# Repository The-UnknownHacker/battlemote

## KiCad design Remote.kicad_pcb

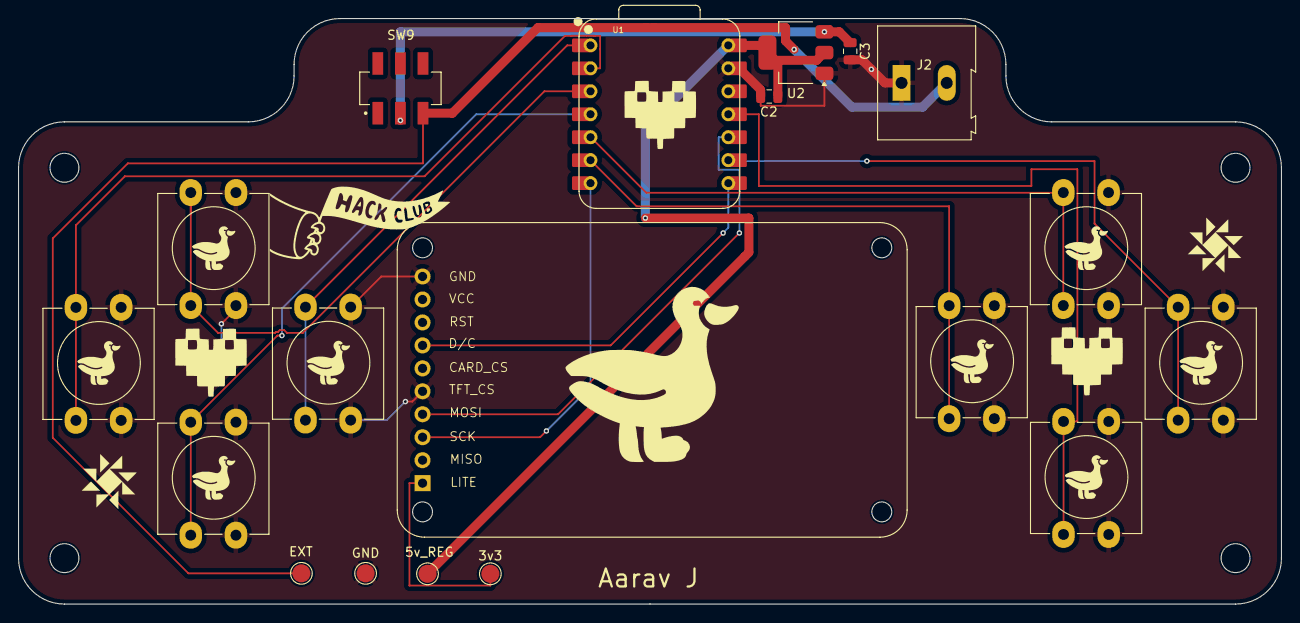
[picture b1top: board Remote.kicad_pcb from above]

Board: 2 copper layers, 139.7 x 64.8 mm, 23 parts (1 on the bottom side), 16 nets.

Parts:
3v3, 5v_REG: TestPoint; TestPoint_Pad_D2.0mm
C2, C3: 22uf; C_0805_2012Metric
EXT: TestPoint; TestPoint_Pad_D2.0mm
GND: TestPoint; TestPoint_Pad_D2.0mm
H1, H2, H3, H4: MountingHole; MountingHole_3.2mm_M3
J2: Extra Battery; TerminalBlock_Altech_AK300-2_P5.00mm
SW1: Right; SW_PUSH-12mm_Wuerth-430476085716
SW2: Left; SW_PUSH-12mm_Wuerth-430476085716
SW3: Top; SW_PUSH-12mm_Wuerth-430476085716
SW4: Bottom; SW_PUSH-12mm_Wuerth-430476085716
SW5: CONFIG1; SW_PUSH-12mm_Wuerth-430476085716
SW6: CONFIG2; SW_PUSH-12mm_Wuerth-430476085716
SW7: CONFIG3; SW_PUSH-12mm_Wuerth-430476085716
SW8: CONFIG4; SW_PUSH-12mm_Wuerth-430476085716
SW9: Slideswitch; SW_JS202011SCQN
U1: XIAO-ESP32-C3-DIP; XIAO-ESP32C3-DIP
U2: AMS1117-5.0; SOT-223-3_TabPin2
U3: 358; MODULE_358

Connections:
+3V3: 3v3.1, U1.12 (VCC_3V3), U3.1 (LITE), U3.8 (RESET), U3.9 (VCC)
+5v_REG: 5v_REG.1, C2.2, U1.14 (VBUS), U2.2 (VO)
EXTERNAL_BAT: EXT.1, J2.2, SW9.3 (C)
GND: C2.1, C3.1, GND.1, J2.1, SW1.2, SW2.2, SW3.2, SW4.2, SW5.2, SW6.2, SW7.2, SW8.2, U1.13 (GND), U2.1 (GND), U3.5 (TFT_CS), U3.10 (GND)
GPIO2: SW1.1, U1.1 (GPIO2/A0/D0)
GPIO3: SW2.1, U1.2 (GPIO3/A1/D1)
GPIO4: SW3.1, U1.3 (GPIO4/A2/D2)
GPIO5: SW4.1, U1.4 (GPIO5/A3/D3)
GPIO6: SW5.1, U1.5 (GPIO6/D4/SDA)
GPIO7: SW6.1, U1.6 (GPIO7/D5/SCL)
GPIO8: SW7.1, U1.9 (GPIO8/D8/SCK)
GPIO9: U1.10 (GPIO9/D9/MISO), U3.4 (MOSI)
GPIO10: SW8.1, U1.11 (GPIO10/D10/MOSI)
GPIO20: U1.8 (GPIO20/D7/RX), U3.7 (D/C)
GPIO21: U1.7 (GPIO21/D6/TX), U3.3 (SCK)
unnamed: C3.2, SW9.2 (B), U2.3 (VI)

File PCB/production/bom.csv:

Designator,Footprint,Quantity,Value,LCSC Part #
"C2, C3",0805,2,22uf,
J2,TerminalBlock_Altech_AK300-2_P5.00mm,1,Extra Battery,
SW1,SW_PUSH-12mm_Wuerth-430476085716,1,Right,
SW2,SW_PUSH-12mm_Wuerth-430476085716,1,Left,
SW3,SW_PUSH-12mm_Wuerth-430476085716,1,Top,
SW4,SW_PUSH-12mm_Wuerth-430476085716,1,Bottom,
SW5,SW_PUSH-12mm_Wuerth-430476085716,1,CONFIG1,
SW6,SW_PUSH-12mm_Wuerth-430476085716,1,CONFIG2,
SW7,SW_PUSH-12mm_Wuerth-430476085716,1,CONFIG3,
SW8,SW_PUSH-12mm_Wuerth-430476085716,1,CONFIG4,
SW9,SW_JS202011SCQN,1,Slideswitch,
U1,XIAO-ESP32C3-DIP,1,XIAO-ESP32-C3-DIP,
U2,SOT-223-3_TabPin2,1,AMS1117-5.0,
U3,MODULE_358,1,358,

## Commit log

2025-07-30 Add all files
2025-08-05 Uodtae
